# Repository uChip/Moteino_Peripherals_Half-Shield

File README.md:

# Moteino Peripherals Half-Shield  

___  

After making breakout boards for the RFM12B & [RFM69](https://github.com/uChip/RFM69W_BOB) and getting a taste of what those radios can do, I decided I would like to experiment more with [Felix Rusu's software](http://www.lowpowerlab.com).  Of particular interest is the software that Felix has created that enables an Arduino based device to be reprogrammed remotely and wirelessly**.  Now I could just buy a few of Felix's fine [Moteinos](http://lowpowerlab.com/moteino/), but I already have a bunch of [Unos](https://www.sparkfun.com/products/11021), [Minis](https://www.sparkfun.com/products/11113), [Pro Micros](https://www.sparkfun.com/products/12640) and such.  So instead I decided to do a new version of the radio breakout board that adds the flash memory chip.  While I was at it, I also added the LED on D9 so that code would work too.  

I call the board a half-shield.  That is because it will plug directly into an UNO header (plus a couple of wires) but takes up only half the pins.  

Here is the Moteino Peripherals Half-Shield plugged into an Arduino clone, the [RedBoard](https://www.sparkfun.com/products/11575) from SparkFun.  

___  

This repo includes Eagle CAD PCB design files for the board.  The board converts the RFM69W radio transceiver from SMT to 0.1" breadboard format and provides [optional] level translation for use with 5V controllers.  Note that you cannot solder the RFM12B or the RFM69CW radio modules to this board.  Use the RFM69W or RFM69HW modules instead.  

The board also has provision on the bottom side for a conforming SOIC-8 package flash memory part such as the Winbond W25X40CLSNIG.  

See the following links for Arduino drivers for the RFM69W and flash memory  
  * https://github.com/LowPowerLab/RFM69  
  * https://github.com/LowPowerLab/SPIFlash  

### 5V Hookup  
Hookup of the breakout board to 5V Arduino SPI connection.  All board components populated.  Solder-jumpers left open.  

	Arduino			Half-Shield  
	  5V	-->		  5V  
	  GND	<-->	  GND  
	  D13	-->		  SCK  
	  D12	<--		  SDO  
	  D11	-->		  SDI  
	  D10	-->		  RSEL  
	  D9	-->		  LED  
	  D8	-->		  FSEL  
	  D2	<--		  IRQ  
	  		<--		  3V3  
 
### 3.3V Hookup  
Hookup of the breakout board to 3.3V Arduino SPI connection.  On PCB populate only radio, flash memory, C1, C2 and C3.  Short the pads on the solder-jumpers.  

	Arduino			Half-Shield  
	  NC	 		  5V  
	  GND	<-->	  GND  
	  D13	-->		  SCK  
	  D12	<--		  SDO  
	  D11	-->		  SDI  
	  D10	-->		  RSEL  
	  D9	-->		  LED  
	  D8	-->		  FSEL  
	  D2	<--		  IRQ  
 	  3.3V	-->		  3V3  

## Order PCBs  

You can order this PCB directly from OSH Park.  Click on the following link.  
  * Radio Breakout - http://oshpark.com/shared_projects/AadEx5fd  

See Bill of Materials file in repo for parts list.  

## Status  
  * PCB layout has been tested to be functional using the Low Power Lab example code for RFM69 and SPIFlash.  

## File Formats  

Design files are in "CadSoft EAGLE PCB Design Software" .brd and .sch formats.  
A free version of the software can be downloaded from www.cadsoftusa.com.  

schematic  

PCB   

## Distribution License  

You may use this PCB design however you like but no liability is accepted.  

## Notes:

** Arduino wireless reprogramming requires a custom bootloader.  Read more about it at http://LowPowerLab.com

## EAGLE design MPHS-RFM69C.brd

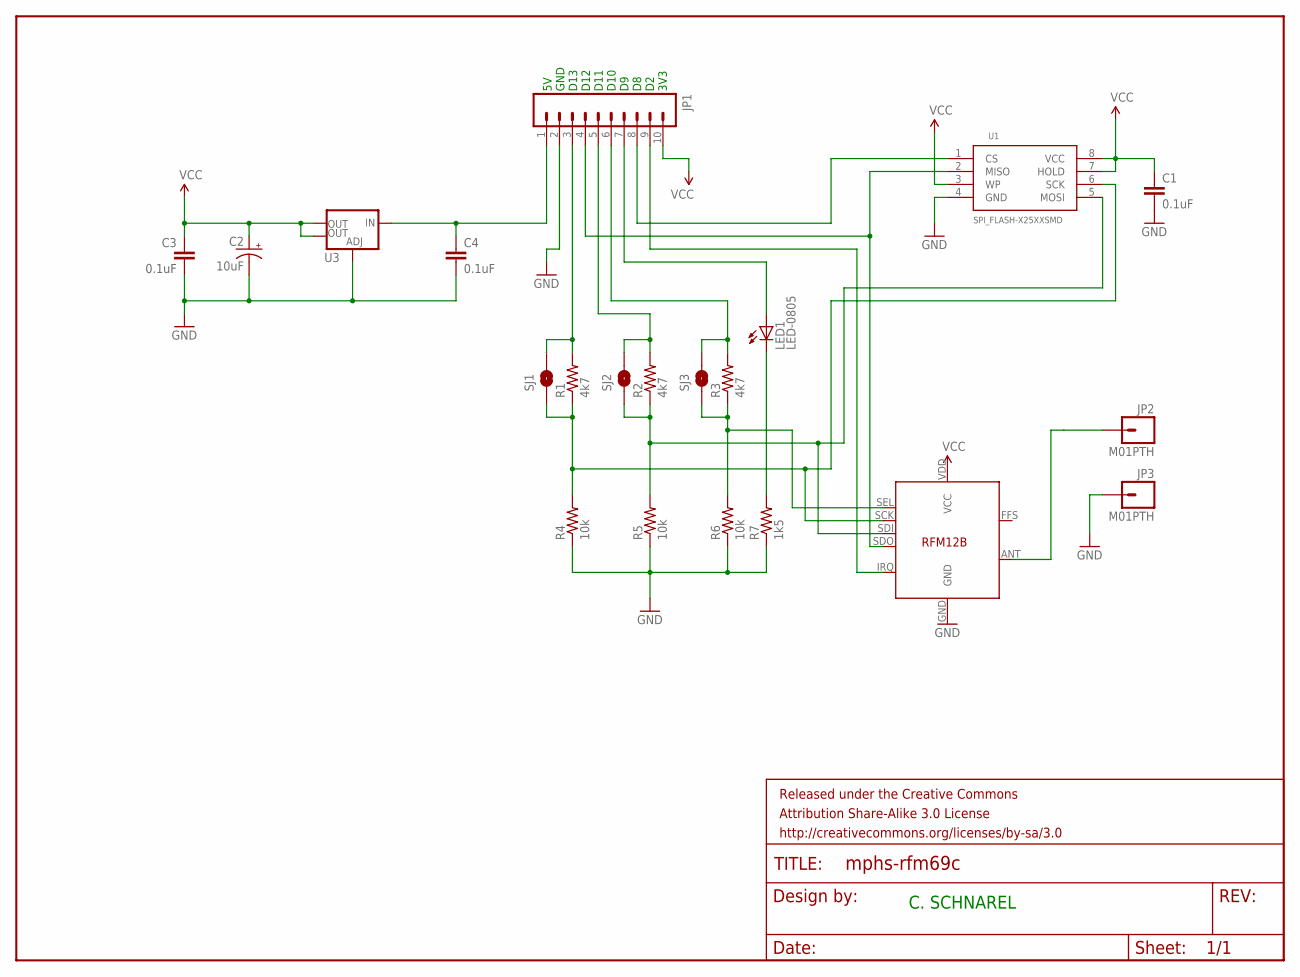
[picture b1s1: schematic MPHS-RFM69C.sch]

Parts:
C1, C3, C4: 0.1uF; 0805
C2: 10uF; 0805-POL
FRAME1: FRAME-LETTER; CREATIVE_COMMONS
JP1: M10"; 1X10
JP2, JP3: M01PTH; 1X01
LED1: LED-0805; 0805-LED
R1, R2, R3: 4k7; 0805
R4, R5, R6: 10k; 0805
R7: 1k5; 0805
SJ1, SJ2, SJ3: SOLDERJUMPERNO; SJ_2S-NO
U1: SPI_FLASH-X25XXSMD; SO08
U3: V_REG_LM1117SOT223; SOT223
U$1: RFM12B

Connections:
GND: C1.2, C2.2 (-), C3.2, C4.2, JP1.2, JP3.1, R4.1, R5.1, R6.1, R7.1, U1.4 (GND), U3.1 (ADJ), U$1.GND
unnamed: R3.1, R6.2, SJ3.1, U$1.SEL
unnamed: C4.1, JP1.1, U3.3 (IN)
unnamed: JP1.4, U1.2 (MISO), U$1.SDO
unnamed: JP1.9, U$1.IRQ
unnamed: R2.1, R5.2, SJ2.1, U1.5 (MOSI), U$1.SDI
unnamed: JP1.3, R1.2, SJ1.2
unnamed: JP1.5, R2.2, SJ2.2
unnamed: JP1.6, R3.2, SJ3.2
unnamed: R1.1, R4.2, SJ1.1, U1.6 (SCK), U$1.SCK
unnamed: JP2.1, U$1.ANT
unnamed: JP1.7, LED1.A
unnamed: JP1.8, U1.1 (CS)
unnamed: LED1.C, R7.2
VCC: C1.1, C2.1 (+), C3.1, JP1.10, U1.3 (WP), U1.7 (HOLD), U1.8 (VCC), U3.2 (OUT), U3.4 (OUT), U$1.VDD (VCC)

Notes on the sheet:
C. SCHNAREL
5V GND D13 D12 D11 D10 D9 D8 D2 3V3

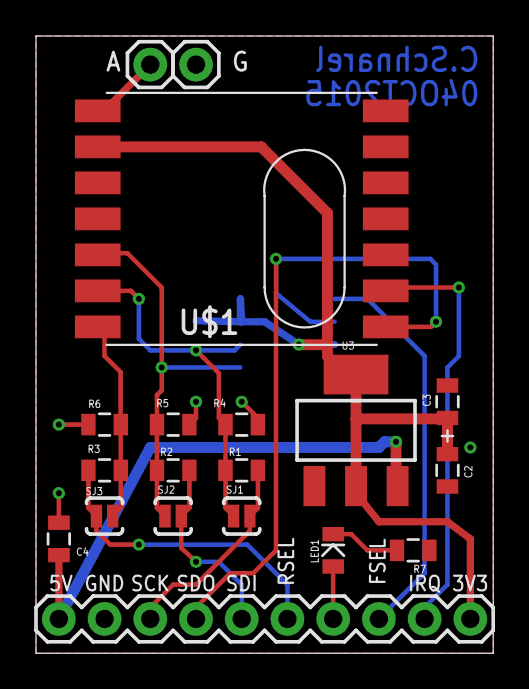
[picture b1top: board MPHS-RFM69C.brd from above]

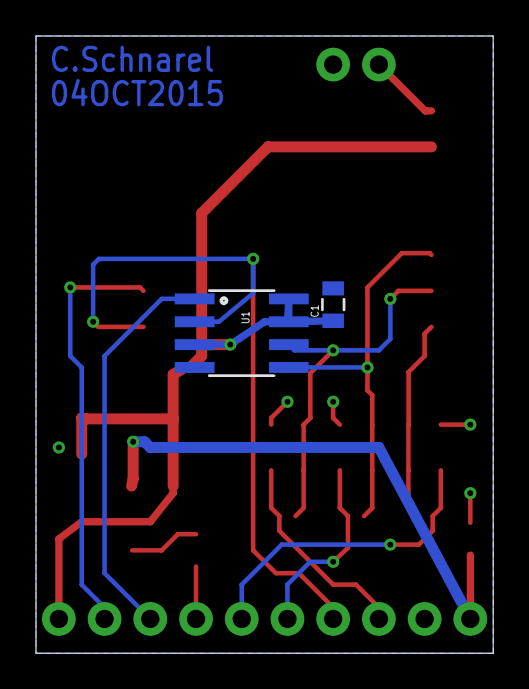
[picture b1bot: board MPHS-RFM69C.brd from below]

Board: 2 copper layers, 25.4 x 34.3 mm, 22 parts (2 on the bottom side), 15 nets.

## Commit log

2014-03-02 Initial Commit
    Half-Shield board for RFM69, flash mem and LED arranged per Moteino I/O
    pins.
2014-03-02 Updated README to use images
2014-03-02 Updates to README
2014-03-02 Adding BOM
2014-03-02 Updated BOM & README
2014-03-07 New photo with LED installed (parts arrived)
    Changed board layout and schematic to have proper LED component. No
    change to actual BOM or circuit. Shot new photo of board with LED
    installed.
2014-03-07 Added more links to README
2014-03-08 README updates
    Added pdf versions of schematic and board for viewing without EagleCAD
2014-03-08 README updates
    Got H & W reversed in new images - fixing.
2014-03-08 Fixed links to PNGs in README
2014-12-12 Updated broken links in README
2015-10-02 Created board variant for RFM69C - NOT TESTED!!!
2015-10-04 Changed VReg to 1117
2015-10-05 Removing Unsupported RFM69C variant

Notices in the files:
parts and their libraries:
SparkFun-Aesthetics: Licensing: CC v3.0 Share-Alike You are welcome to use this library for commercial purposes.
SparkFun-Aesthetics: Released under the Creative Commons Attribution Share-Alike 3.0 License
SparkFun-Aesthetics: http://creativecommons.org/licenses/by-sa/3.0
